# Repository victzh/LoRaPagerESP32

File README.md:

# LoRaPagerESP32

This is an experimenter board using Blackberry Q10 keyboard, LoRa module RFM95, ESP32-Wroom module, and several versions of displays.

This board is just ordered from PCB manufacturer and never been built, so use with caution.

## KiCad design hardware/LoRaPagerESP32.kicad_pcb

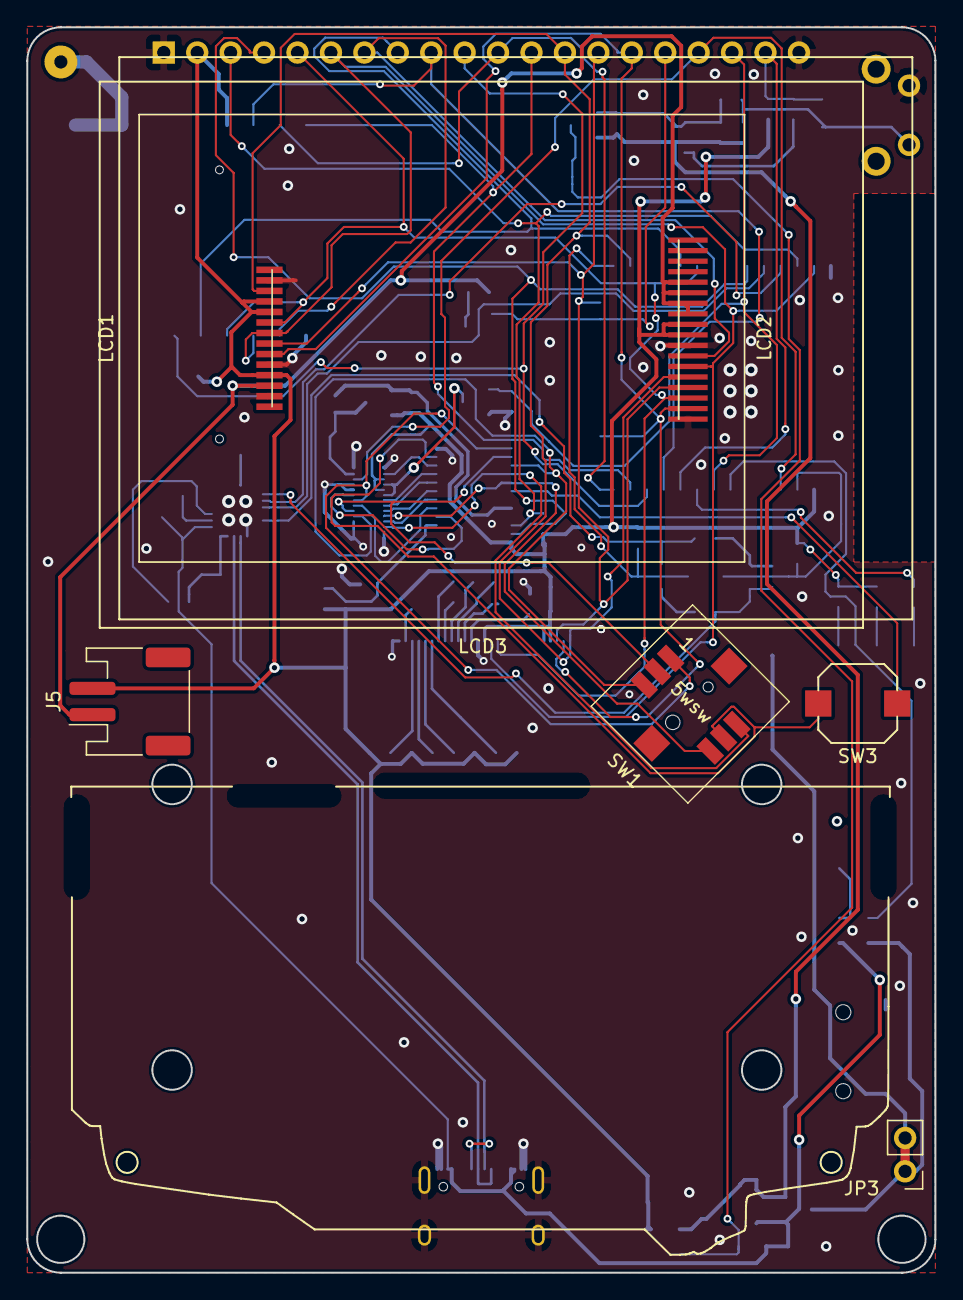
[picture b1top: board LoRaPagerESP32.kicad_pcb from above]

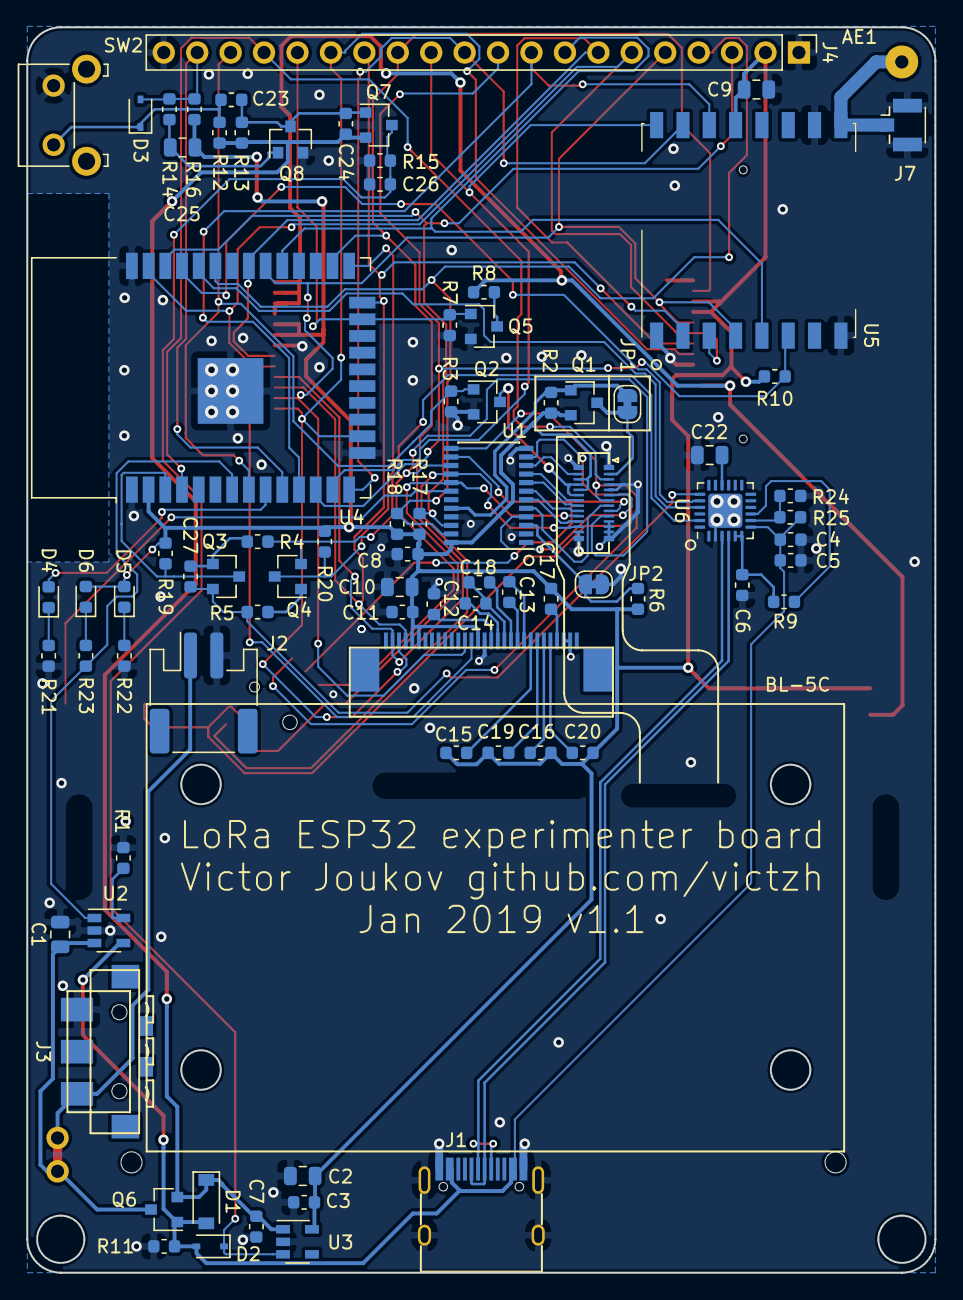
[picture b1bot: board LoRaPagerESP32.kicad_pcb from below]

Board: 2 copper layers, 69.0 x 94.6 mm, 89 parts (81 on the bottom side), 79 nets.

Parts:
AE1: Antenna; SolderWirePad_1x01_Drill1mm
BL-5C: BL-5C
C1, C2, C10, C25: 10uF; C_0805_2012Metric
C3, C5, C6, C7, C12, C13, C14, C15, C16, C17, C18, C19, C20, C23: 1uF; C_0603_1608Metric
C4, C8, C11, C24, C26, C27: 0.1uF; C_0603_1608Metric
C9, C22: 4.7uF; C_0805_2012Metric
D1: D_Schottky; D_SOD-123
D2, D3: D; D_SOD-323
D4, D5, D6: LED; LED_0603_1608Metric
J1: USB_C_Receptacle_USB2.0; USB_C_Receptacle_GT-USB-7010
J2, J5: Conn_01x02; JST_PH_S2B-PH-SM4-TB_1x02-1MP_P2.00mm_Horizontal
J3: Conn_01x03; BC-4-3P-1746142-1
J4: Conn_01x20_Male; PinHeader_1x20_P2.54mm_Vertical
J7: Conn_Coaxial; U.FL_Hirose_U.FL-R-SMT-1_Vertical
JP1, JP2: Jumper_NC_Small; SolderJumper-2_P1.3mm_Bridged_RoundedPad1.0x1.5mm
JP3: Jumper_NC_Small; Test_bridge_2.54mm
KBD1: Keyboard_BBQ10KBD; BBQ10KBD
LCD1: Z240IT010
LCD2: JD-T1800
LCD3: ERC12864FS-12.1; ERC12864-12.1
Q1: BSS84; SOT-23
Q2: BSS138; SOT-23
Q3, Q4: Q_NPN_BEC; SOT-23
Q5, Q8: Q_NMOS_GSD; SOT-23
Q6, Q7: Q_PMOS_GSD; SOT-23
R1: 5k; R_0603_1608Metric
R2, R3, R4, R5, R6, R7, R9, R10, R12, R19, R20: 10k; R_0603_1608Metric
R8: 22R; R_0603_1608Metric
R11, R13, R15, R16: 100k; R_0603_1608Metric
R14: 300k; R_0603_1608Metric
R17, R18: 4.7k; R_0603_1608Metric
R21, R22, R23: 1k; R_0603_1608Metric
R24: 47.5k; R_0603_1608Metric
R25: 22.1k; R_0603_1608Metric
SW1: 5W_SW; 5WAY_sw
SW2: SW_Push; SW_Tactile_SKHH_Angled
SW3: SW_Push; 1TS009
U1: PCA9555PW,118; TSSOP-24_4.4x7.8mm_P0.65mm
U2: MCP73831-2-OT; SOT-23-5
U3: AP2112K-3.3; SOT-23-5
U4: ESP-32_WROOM32; ESP32-WROOM-32
U5: RFM96; HOPERF_RFM9XW_SMD
U6: CP2104; QFN-24-1EP_4x4mm_P0.5mm_EP2.6x2.6mm

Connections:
+3V3: C2.1, C3.1, C8.1, C9.1, C10.2, C11.2, C15.2, C16.2, C17.2, C19.2, C20.2, C25.1, D5.2, D6.2, J4.2, J5.2, KBD1.24, KBD1.26, LCD1.9, LCD1.10, LCD2.4, LCD2.10, LCD2.11, LCD3.5, LCD3.6, LCD3.15, Q1.2, R2.1, R6.1, R10.1, R16.1, R17.1, R18.1, R19.1, R20.1, U1.24, U3.5, U4.2, U5.13
+BATT: C1.1, JP3.1, Q6.3, U2.3
/ANT: AE1.1, J7.1, U5.9
/CHARGE_STAT: R23.1, U2.1, U4.7
/DISP_CS: J4.13, LCD1.5, LCD2.12, LCD3.2, U4.26
/DISP_DC: J4.14, LCD1.4, LCD2.7, LCD3.4, U4.24
/DISP_LED: J4.16, Q5.1, R7.1, U4.23
/DISP_RESET: J4.15, LCD1.2, LCD2.6, LCD3.3, U4.16
/DTR: Q4.2, R4.2, U6.23
/Display/LEDK: J5.1, LCD1.11, LCD1.12, LCD1.13, LCD1.14, LCD2.3, R8.1
/GPIO0: Q4.3, R20.2, U4.25
/HEARTBEAT_LED: D4.2, U4.9
/KB_LED: J4.18, Q2.1, R3.1, U4.8
/KB_MIC: J4.17, KBD1.3, U4.4
/Keyboard/KB_COL1: KBD1.7, SW1.1, U1.13
/Keyboard/KB_COL2: KBD1.9, SW1.2, U1.14
/Keyboard/KB_COL3: KBD1.10, SW1.3, U1.15
/Keyboard/KB_COL4: KBD1.17, SW1.4, U1.16
/Keyboard/KB_COL5: KBD1.19, SW1.6, U1.17
/Keyboard/KB_COL6: SW3.1, U1.18
/Keyboard/KB_ROW1: KBD1.6, U1.4
/Keyboard/KB_ROW2: KBD1.8, U1.5
/Keyboard/KB_ROW3: KBD1.18, U1.6
/Keyboard/KB_ROW4: KBD1.20, U1.7
/Keyboard/KB_ROW5: KBD1.21, U1.8
/Keyboard/KB_ROW6: KBD1.22, U1.9
/Keyboard/KB_ROW7: KBD1.27, U1.10
/Keyboard/KB_ROW8: SW1.5, SW3.2, U1.11
/Keyboard/MIC_POWER: JP1.2, Q1.1, R2.2, U1.20
/MISO: J4.7, LCD1.7, U4.31, U5.2
/MOSI: J4.6, LCD1.6, LCD2.8, LCD3.14, U4.37, U5.3
/POWER_CTRL: D3.2, J4.19, R14.1, R16.2, U4.10
/Power/EN: C26.1, D2.1, Q7.3, R15.1, U3.3
/Power/VIN: C7.1, C24.1, D1.1, Q6.2, Q7.2, R12.1, R13.1, U3.1
/RESET: Q3.3, R19.2, U4.3
/RFM_CS: J4.8, U4.29, U5.5
/RFM_DIO1: J4.11, U4.14, U5.15
/RFM_DIO2: J4.12, U4.13, U5.16
/RFM_INT: J4.9, U4.11, U5.14
/RFM_RESET: J4.10, R10.2, U4.12, U5.6
/RTS: C27.2, Q3.2, R5.2, U6.19
/RXD: U4.35, U6.20
/SCK: J4.5, LCD1.3, LCD2.9, LCD3.13, U4.30, U5.4
/SCL: J4.3, R17.2, U1.22, U4.36
/SDA: J4.4, R18.2, U1.23, U4.33
/TXD: U4.34, U6.21
/USB/D_N: J1.A7, J1.B7, U6.4
/USB/D_P: J1.A6, J1.B6, U6.3
GND: C1.2, C2.2, C3.2, C4.1, C5.1, C6.2, C7.2, C8.2, C9.2, C10.1, C11.1, C12.2, C22.2, C26.2, J1.A1, J1.A12, J1.B1, J1.B12, J1.S1, J2.2, J3.3, J4.1, J4.20, J7.2, JP2.2, KBD1.1, KBD1.4, KBD1.5, KBD1.11, KBD1.12, KBD1.13, KBD1.14, KBD1.15, KBD1.16, KBD1.28, LCD1.1, LCD1.8, LCD2.2, LCD2.5, LCD2.13, LCD3.16, LCD3.28, LCD3.29, Q2.2, Q5.2, Q8.2, R1.2, R3.2, R7.2, R11.2, R15.2, R21.1, R22.1, R24.2, SW2.2, U1.2, U1.12, U1.21, U2.2, U3.2, U4.1, U4.15, U4.38, U4.39, U5.1, U5.8, U5.10, U6.2, U6.25
unnamed: C12.1, LCD3.17
unnamed: C13.1, LCD3.22
unnamed: C13.2, LCD3.21
unnamed: C14.1, LCD3.18
unnamed: C14.2, C18.2, LCD3.19
unnamed: C15.1, LCD3.23
unnamed: C16.1, LCD3.25
unnamed: C17.1, LCD3.27
unnamed: C18.1, LCD3.20
unnamed: C19.1, LCD3.24
unnamed: C20.1, LCD3.26
unnamed: C22.1, U6.16
unnamed: C23.1, C24.2, Q7.1, Q8.3, R13.2
unnamed: C23.2, D3.1, R12.2, SW2.1
unnamed: C25.2, Q8.1, R14.2
unnamed: C27.1, Q3.1, R4.1
unnamed: D4.1, R21.2
unnamed: D5.1, R22.2
unnamed: D6.1, R23.2
unnamed: J2.1, J3.1, JP3.2
unnamed: JP1.1, KBD1.2, Q1.3
unnamed: JP2.1, R6.2, U1.3
unnamed: KBD1.23, KBD1.25, Q2.3
unnamed: Q4.1, R5.1
unnamed: Q5.3, R8.2
unnamed: R1.1, U2.5
unnamed: R9.2, U6.9
unnamed: R24.1, R25.2, U6.8
VBUS: C4.2, C5.2, D1.2, D2.2, J1.A4, J1.A9, J1.B4, J1.B9, Q6.1, R11.1, R25.1, U2.4, U6.7
VDD: C6.1, R9.1, U6.5, U6.6

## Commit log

2018-12-16 Fix library paths to relative
2018-12-27 Move global symbol libraries to project
2018-12-27 Ignored symbol libraries added
2018-12-27 Fix sch files to not use rescue symbol lib
2019-01-02 Version 1.1
